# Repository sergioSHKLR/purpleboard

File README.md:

<p align="center">
  <picture>
    <source media="(prefers-color-scheme: dark)" srcset="docs/brand/purpleboard-tile-dark.svg">
    
  </picture>
</p>

<h1 align="center">PurpleBoard</h1>

<p align="center">Based on <a href="https://github.com/tholtman1-del/deadboard">DEADBOARD by tholtman1-del</a> (Apache-2.0). This fork adds Xbox controller support for the Navy 2M soldering trainer; see <a href="ROADMAP.md">ROADMAP.md</a>.</p>

<p align="center"><b>Board-level repair trainer.</b> Diagnose and repair simulated circuit boards on a realistic bench, right in the browser.</p>

<p align="center">
  <b><a href="https://sergioshklr.github.io/purpleboard/">▶ Try it in your browser</a></b> ·
  <a href="https://sergioshklr.github.io/purpleboard/learn.html">Repair curriculum &amp; guides</a> ·
  <a href="https://sergioshklr.github.io/purpleboard/boardview.html">Boardview &amp; KiCad viewer</a> ·
  <a href="https://github.com/tholtman1-del/deadboard/releases/latest">Watch the 1-minute showcase (MP4)</a>
</p>

---

PurpleBoard puts a broken board on your bench and gives you the tools a repair technician uses.
You probe, reason, rework and prove the fix. The circuit runs on a SPICE-style simulator, so
the meter reads what the circuit really does, not a scripted answer.

- **Real instruments.** Multimeter (V, Ω, diode, capacitance, current in series), bench supply
  with current limit, oscilloscope, thermal camera, freeze spray, IPA, rosin.
- **Real rework.** Soldering iron, hot air, desoldering wick, trace cutter, jumper wire, fitting
  new parts. Joints can be cold, pads can lift, and a blob in the wrong place shorts a rail.
- **Real boards.** Besides hand-made training boards it imports KiCad designs. Two
  open-hardware boards ship as demos: the **MNT Reform 2** laptop mainboard (530 parts) and an
  **Antmicro Jetson** baseboard (392 parts).
- **Repair challenges.** Each scenario has test-bench objectives. Pass them all, with the circuit
  back to its reference design, and an encrypted flag unlocks. Build and share your own in the
  Author tab: plant shorts, opens, leaks, drift and intermittent faults.
- **Endless practice.** Fixed a board? Generate a new problem on it: 1–3 random faults (cracked
  traces, bridges, cold joints, reversed, wrong, missing or dead parts; leaks and drift on SPICE),
  each checked to fail the bench without burning anything, with notes that go from where to look
  to the fix.
- **Walkthrough videos.** Every premade scene has a "how to approach" video and a separate,
  spoiler-gated solution video, recorded from the real app.
- **Honest numbers.** Where a value is estimated or a waveform is synthesized, the app says so.

## Run it

You need Node.js 20+ and a recent browser. The bench draws with WebGPU where the browser offers
it and falls back to WebGL2 otherwise (blocklisted GPUs, older Safari, Firefox without WebGPU);
add `?renderer=webgl2` or `?renderer=webgpu` to the app URL to force one.

```bash
npm install
npm run dev        # http://localhost:5173
npm test           # simulator, import, physics and scenario tests
npm run build      # static site in dist/
```

## Scenarios

| | |
|---|---|
| **Beginner** | First Light, Cold Joint 101, Solder Bridge 101, One-Way LED, Resistor & Ohm's Law, Voltage Divider 101 |
| **Training boards** | Bridge Troll, Backwards Day, Ghost Short, Smoke Test, The Sagging Rail |
| **Open-hardware demos** | MNT Reform 2 · dead 3.3 V rail; Antmicro baseboard · no 3.3 V, flaky 5 V |

Import your own board: KiCad `.kicad_pcb`, a boardview (OpenBoardView/TopTest or BRD2 `.brd`,
Tebo-ICT `.tvw`), or a shared `.pcbfix.json` challenge.

Languages: English and Russian (picked from the browser, or with the language menu). To add one,
see [docs/TRANSLATING.md](docs/TRANSLATING.md).

## Feedback

Found a bug or have an idea? Press the speech-bubble button in the bench (or **Feedback** on the
homepage). No account needed: the message is emailed to the maintainer, with optional technical
details (browser, GPU, board, view) so the problem can be reproduced. With a GitHub account you can
also [open an issue](https://github.com/sergioSHKLR/purpleboard/issues/new).

The form delivers through [FormSubmit](https://formsubmit.co). The destination is a build setting,
`VITE_FEEDBACK_TO` (an address, or the alias FormSubmit sends after its one-time activation): put it
in `.env.local` for local builds, and in the repository variable `FEEDBACK_TO` for GitHub Pages.
Without it, the form falls back to a prefilled GitHub issue.

## Docs

- [docs/DEMOS.md](docs/DEMOS.md): how the demo boards are built from upstream KiCad sources
- [docs/VIDEOS.md](docs/VIDEOS.md): how the walkthrough videos are recorded
- [docs/BRAND.md](docs/BRAND.md): name, logo, colour, type and voice
- [docs/SIMULATION_HANDOFF.md](docs/SIMULATION_HANDOFF.md): simulator architecture, models and open items
- Mods ([on the website](https://sergioshklr.github.io/purpleboard/modding.html)): [docs/MODDING.md](docs/MODDING.md) (guide),
  [docs/MOD_REFERENCE.md](docs/MOD_REFERENCE.md), [docs/CODE_MODS.md](docs/CODE_MODS.md),
  [docs/MOD_SAFETY.md](docs/MOD_SAFETY.md), [docs/MODS_FOR_AGENTS.md](docs/MODS_FOR_AGENTS.md);
  design and security review: [docs/MOD_PLATFORM.md](docs/MOD_PLATFORM.md)
- [AGENTS.md](AGENTS.md): for AI coding agents working on this repository

## Licence

PurpleBoard, like the DEADBOARD project it is based on (https://github.com/tholtman1-del/deadboard), is licensed under the [Apache License 2.0](LICENSE). The demo boards in
`public/demos/` keep the licences of their source designs (CERN-OHL-S-2.0, CERN-OHL-P-2.0 and Apache-2.0); see
[NOTICE](NOTICE) and [public/demos/NOTICE.txt](public/demos/NOTICE.txt). MNT Reform is a
trademark of MNT Research GmbH, Jetson a trademark of NVIDIA and ESP32 a trademark of Espressif
Systems; no endorsement is implied.

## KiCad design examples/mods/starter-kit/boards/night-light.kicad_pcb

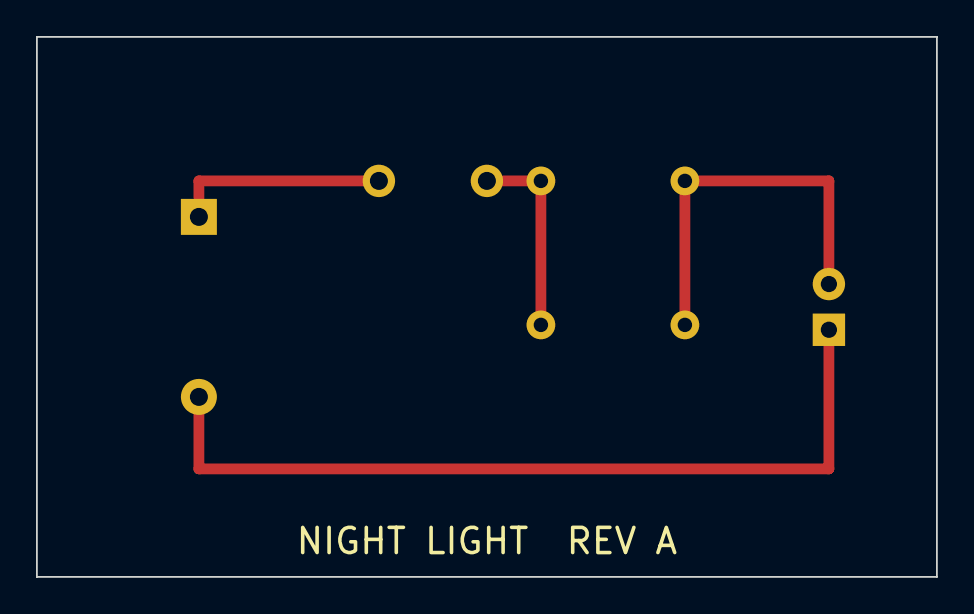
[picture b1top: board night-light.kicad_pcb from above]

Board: 0 copper layers, 50.0 x 30.0 mm, 5 parts (0 on the bottom side), 4 nets.

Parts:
BT1: 3V; BatteryHolder_2xAA
D1: Red; LED_D5.0mm
R1, R2: R_Axial_DIN0207
SW1: PUSH; SW_PUSH_6mm

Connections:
GND: BT1.2, D1.1
LED_A: D1.2, R1.2, R2.2
SW: R1.1, R2.1, SW1.2
VBAT: BT1.1, SW1.1
